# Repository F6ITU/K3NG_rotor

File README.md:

# K3NG_rotor
Yet another K3NG rotator controler pcb

This implementation is based on an Arduino Mega board and a pair of 4x relay boards to drive an AZ-EL antenna system.

Most basic functions are directly driven via Molex KK 254 connectors (up/down, right/left, lcd display output, GPS input, *
I2C extensions... etc). All other "vacant" gpio could be used via solderpads. 

Board could be powered from 8 to 15V 

Source code and wiki should be downloaded at 

https://github.com/k3ng/k3ng_rotator_controller

# Notes de montage

* Les barrettes de contact au pas de 2,54 doivent être soudées après les avoir insérées dans les connecteur gpio de l’Arduino. La série de brasure doit donc être effectuée avec le module MCU en place, lequel servira ainsi de gabarit d’alignement pour les broches. Sans cette précaution, il sera quasiment impossible d’installer l’Arduino sur la carte. 

* Le régulateur de tension doit être le circuit à souder avant tout autre composant. Les deux principaux condensateurs de filtrage sont très proche du 7805 et gêneraient la brasure ce celui-ci s’il était monté a posteriori

* Tous les connecteurs Molex kk254 ne sont pas nécessairement à installer. C’est le cas notamment des entrées gpio « serial » de 0 à 3, qui peuvent être remplacés par de simples jumpers les reliant aux sorties des périphériques installés. Cela permet de choisir sur quel port seront reliés les modules  gps ou Nextion s’il y a lieu

* Toutes les E/S de l’Arduino sont doublées par une rangée de contacts au pas de 2,54, laissant libre toute possibilité d’ajouts de modules exotiques. 

* Les modules « 4 relais » disponibles sur Amazon ou AliExpress sont généralement livrés avec un connecteur « broches  carte à fils » au pas de 2,54mm orientés vers le dessus de la carte. Il est nécessaire de les dessouder et de les remplacer par un connecteur identique, mais soudé « coté piste ». Le shield K3NG doit, pour sa part, être équipé d’un connecteur femelle « carte à carte » pour recevoir la ou les cartes relais en « piggy back ». 

* Deux cartes relais peuvent être installées pour piloter une paire de moteurs azimut/élévation. Prévoir deux entretoises d’une hauteur équivalente aux connecteurs de liaison. 

* ATTENTION : les relais sont commandés « 2 à 2 », soit pour assurer une coupure courants forts, soit pour être utilisés en inverseur (un contact ouvert et un contact fermé au repos, et lycée de Versailles au travail). Cette configuration est notamment nécessaire pour commander les rotor Kantronic/Yaesu/Toyomura d’ancienne génération (split phase ou à phase divisée)

 * Une BOM interactive est disponible sur ce Github dans le répertoire BOM du même métal

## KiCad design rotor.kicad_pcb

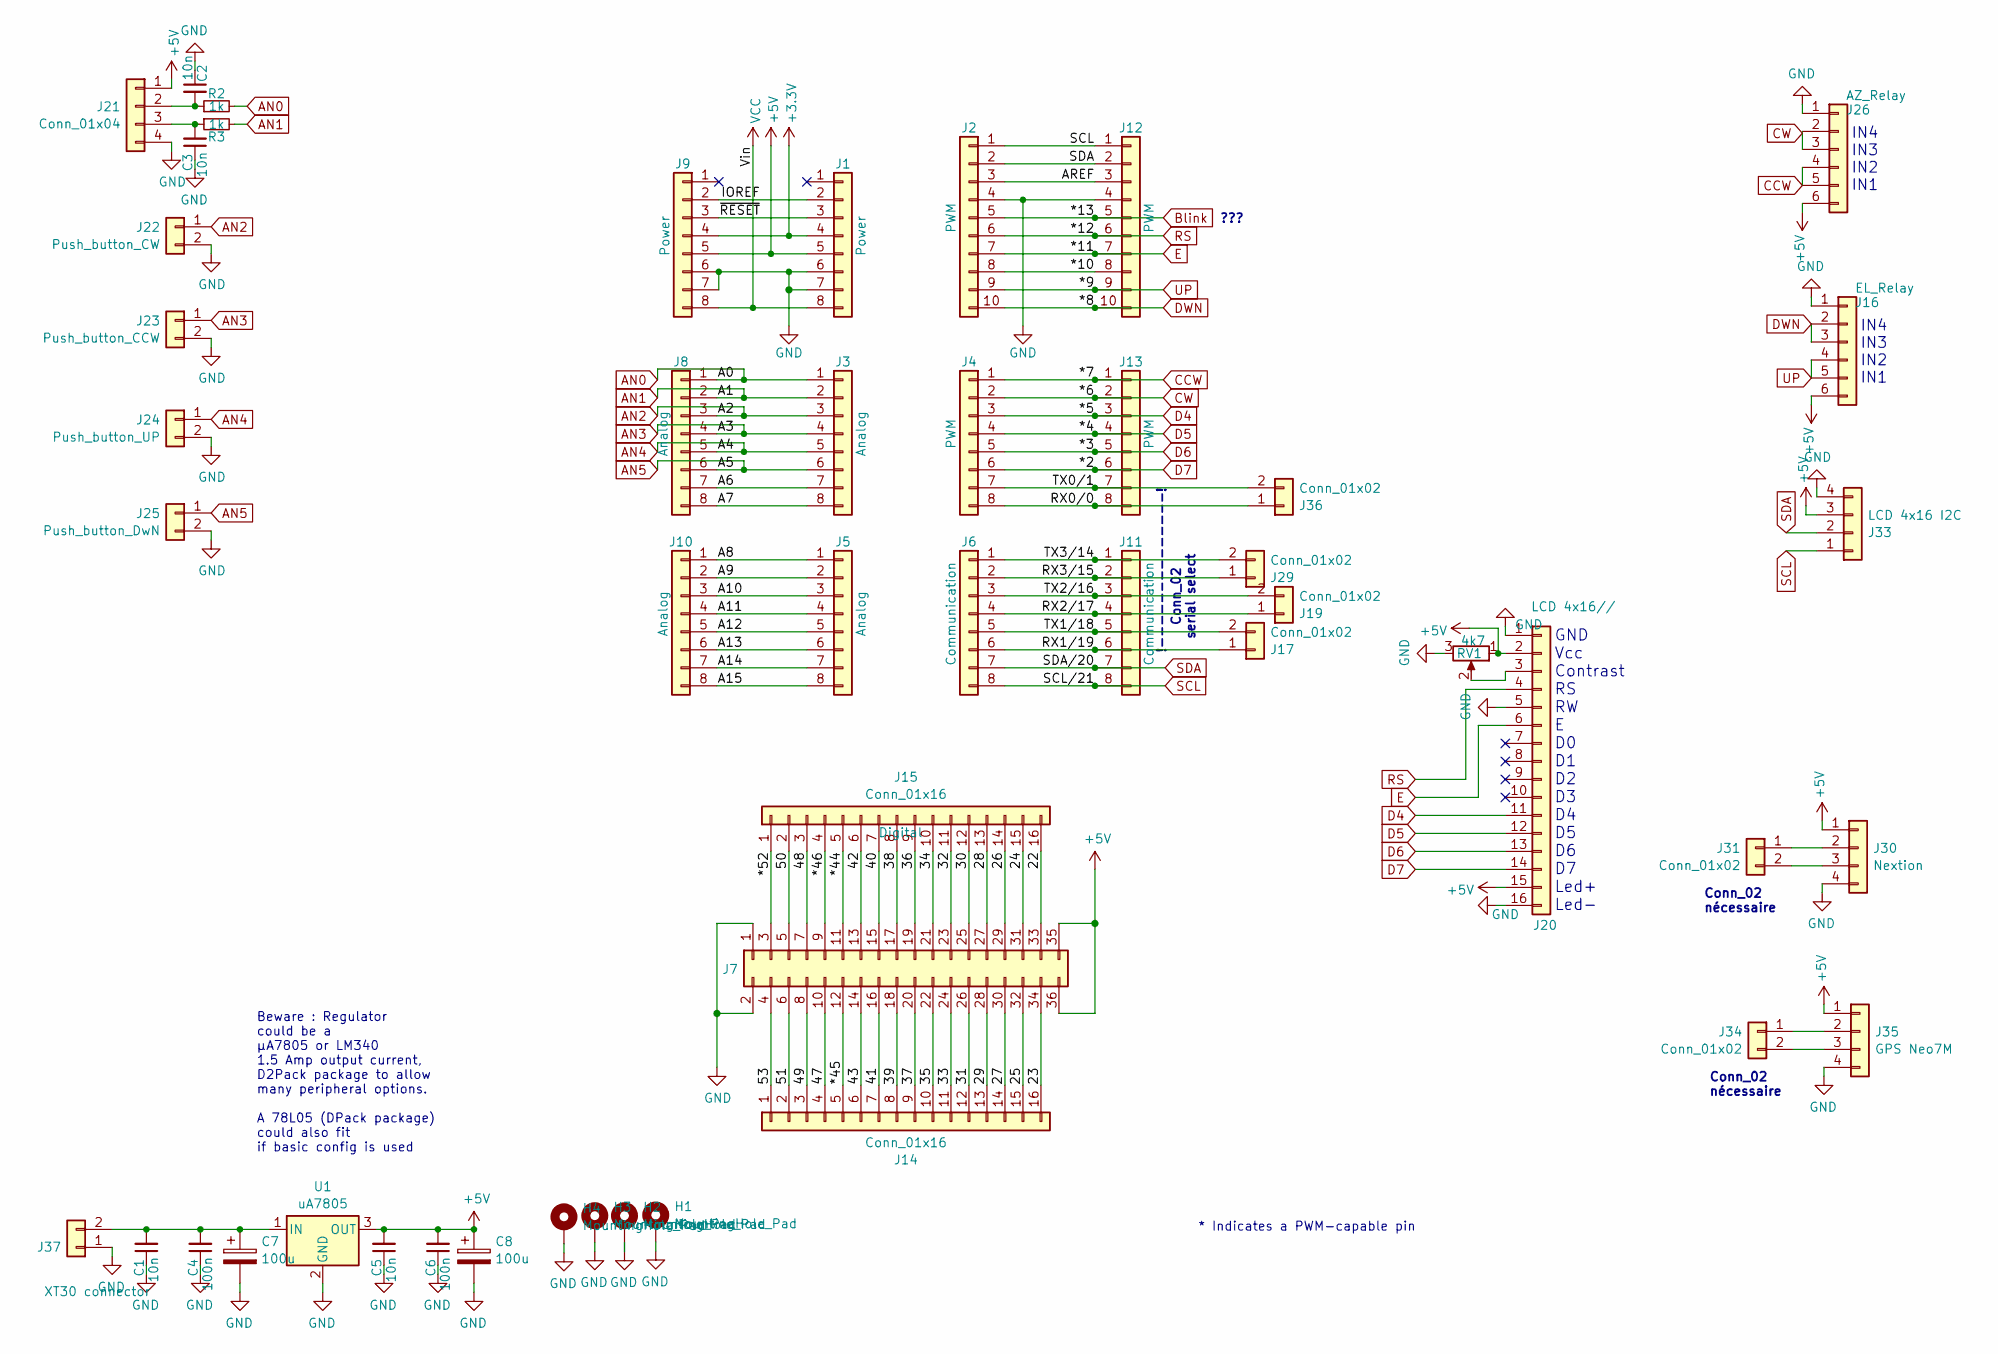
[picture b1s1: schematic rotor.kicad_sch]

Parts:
C1, C2, C3, C5: 10n; C_0805_2012Metric_Pad1.18x1.45mm_HandSolder
C4, C6: 100n; C_0805_2012Metric_Pad1.18x1.45mm_HandSolder
C7, C8: 100u; CP_Elec_10x12.6
H1, H2, H3, H4: MountingHole_Pad; MountingHole_3.5mm_Pad
J1, J9: Power; PinSocket_1x08_P2.54mm_Vertical
J2, J12: PWM; PinSocket_1x10_P2.54mm_Vertical
J3, J8: Analog; PinHeader_1x08_P2.54mm_Vertical
J4, J13: PWM; PinSocket_1x08_P2.54mm_Vertical
J5, J10: Analog; PinSocket_1x08_P2.54mm_Vertical
J6, J11: Communication; PinSocket_1x08_P2.54mm_Vertical
J7: Digital; PinSocket_2x18_P2.54mm_Vertical
J14, J15: Conn_01x16; PinHeader_1x16_P2.54mm_Vertical
J16: EL_Relay; PinSocket_1x06_P2.54mm_Vertical
J17, J19, J29, J31, J34, J36: Conn_01x02; Molex_KK-254_AE-6410-02A_1x02_P2.54mm_Vertical
J20: LCD 4x16//; Molex_KK-254_AE-6410-16A_1x16_P2.54mm_Vertical
J21: Conn_01x04; Molex_KK-254_AE-6410-04A_1x04_P2.54mm_Vertical
J22: Push_button_CW; Molex_KK-254_AE-6410-02A_1x02_P2.54mm_Vertical
J23: Push_button_CCW; Molex_KK-254_AE-6410-02A_1x02_P2.54mm_Vertical
J24: Push_button_UP; Molex_KK-254_AE-6410-02A_1x02_P2.54mm_Vertical
J25: Push_button_DwN; Molex_KK-254_AE-6410-02A_1x02_P2.54mm_Vertical
J26: AZ_Relay; PinSocket_1x06_P2.54mm_Vertical
J30: Nextion; Molex_KK-254_AE-6410-04A_1x04_P2.54mm_Vertical
J33: LCD 4x16 I2C; Molex_KK-254_AE-6410-04A_1x04_P2.54mm_Vertical
J35: GPS Neo7M; Molex_KK-254_AE-6410-04A_1x04_P2.54mm_Vertical
J37: XT30 connector; AMASS_XT30U-F_1x02_P5.0mm_Vertical
R2, R3: 1k; R_0805_2012Metric_Pad1.20x1.40mm_HandSolder
RV1: 4k7; Potentiometer_Bourns_TC33X_Vertical
U1: uA7805; TO-263-3_TabPin2

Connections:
+3V3: J1.4, J9.4
+5V: C5.2, C6.2, C8.1, J1.5, J7.35, J7.36, J9.5, J16.6, J20.2, J20.15, J21.1, J26.6, J30.1, J33.3, J35.1, RV1.1, U1.3 (OUT)
/22: J7.33, J15.16
/23: J7.34, J14.16
/24: J7.31, J15.15
/25: J7.32, J14.15
/26: J7.29, J15.14
/27: J7.30, J14.14
/28: J7.27, J15.13
/29: J7.28, J14.13
/30: J7.25, J15.12
/31: J7.26, J14.12
/32: J7.23, J15.11
/33: J7.24, J14.11
/34: J7.21, J15.10
/35: J7.22, J14.10
/36: J7.19, J15.9
/37: J7.20, J14.9
/38: J7.17, J15.8
/39: J7.18, J14.8
/40: J7.15, J15.7
/41: J7.16, J14.7
/42: J7.13, J15.6
/43: J7.14, J14.6
/47: J7.10, J14.4
/48: J7.7, J15.3
/49: J7.8, J14.3
/50: J7.5, J15.2
/51: J7.6, J14.2
/53: J7.4, J14.1
/*10: J2.8, J12.8
/*44: J7.11, J15.5
/*45: J7.12, J14.5
/*46: J7.9, J15.4
/*52: J7.3, J15.1
/A6: J3.7, J8.7
/A7: J3.8, J8.8
/A8: J5.1, J10.1
/A9: J5.2, J10.2
/A10: J5.3, J10.3
/A11: J5.4, J10.4
/A12: J5.5, J10.5
/A13: J5.6, J10.6
/A14: J5.7, J10.7
/A15: J5.8, J10.8
/AREF: J2.3, J12.3
/IOREF: J1.2, J9.2
/RX0/0: J4.8, J13.8, J36.1
/RX1/19: J6.6, J11.6, J17.1
/RX2/17: J6.4, J11.4, J19.1
/RX3/15: J6.2, J11.2, J29.1
/TX0/1: J4.7, J13.7, J36.2
/TX1/18: J6.5, J11.5, J17.2
/TX2/16: J6.3, J11.3, J19.2
/TX3/14: J6.1, J11.1, J29.2
/~RESET: J1.3, J9.3
AN0: J3.1, J8.1, R2.2
AN1: J3.2, J8.2, R3.2
AN2: J3.3, J8.3, J22.1
AN3: J3.4, J8.4, J23.1
AN4: J3.5, J8.5, J24.1
AN5: J3.6, J8.6, J25.1
Blink: J2.5, J12.5
CCW: J4.1, J13.1, J26.4, J26.5
CW: J4.2, J13.2, J26.2, J26.3
D4: J4.3, J13.3, J20.11
D5: J4.4, J13.4, J20.12
D6: J4.5, J13.5, J20.13
D7: J4.6, J13.6, J20.14
DWN: J2.10, J12.10, J16.2, J16.3
E: J2.7, J12.7, J20.6
GND: C1.1, C2.1, C3.1, C4.1, C5.1, C6.1, C7.2, C8.2, H1.1, H2.1, H3.1, H4.1, J1.6, J1.7, J2.4, J7.1, J7.2, J9.6, J9.7, J12.4, J16.1, J20.1, J20.5, J20.16, J21.4, J22.2, J23.2, J24.2, J25.2, J26.1, J30.4, J33.4, J35.4, J37.1, RV1.3, U1.2 (GND)
unnamed: J20.3, RV1.2
unnamed: C2.2, J21.2, R2.1
unnamed: C3.2, J21.3, R3.1
unnamed: J30.2, J31.1
unnamed: J30.3, J31.2
unnamed: J34.1, J35.2
unnamed: J34.2, J35.3
unnamed: C1.2, C4.2, C7.1, J37.2, U1.1 (IN)
RS: J2.6, J12.6, J20.4
SCL: J2.1, J6.8, J11.8, J12.1, J33.1
SDA: J2.2, J6.7, J11.7, J12.2, J33.2
UP: J2.9, J12.9, J16.4, J16.5
VCC: J1.8, J9.8

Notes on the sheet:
???
IN4 IN3 IN2 IN1
!--------------! Conn_02 serial select
Conn_02 nécessaire
GND Vcc Contrast RS RW E D0 D1 D2 D3 D4 D5 D6 D7 Led+ Led-
* Indicates a PWM-capable pin
Beware : Regulator could be a µA7805 or LM340 1.5 Amp output current, D2Pack package to allow many peripheral options. A 78L05 (DPack package) could also fit if basic config is used

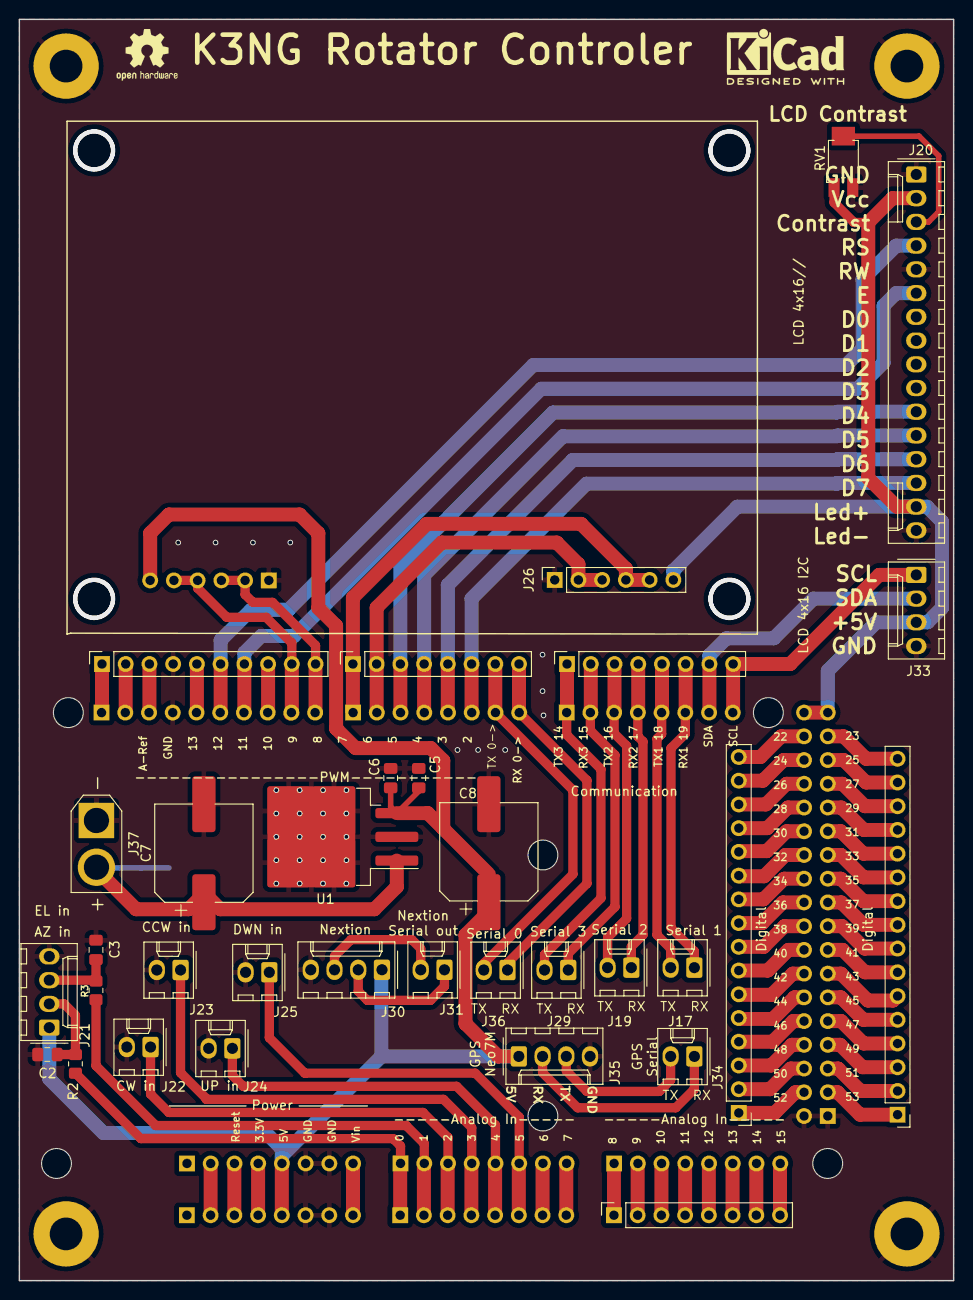
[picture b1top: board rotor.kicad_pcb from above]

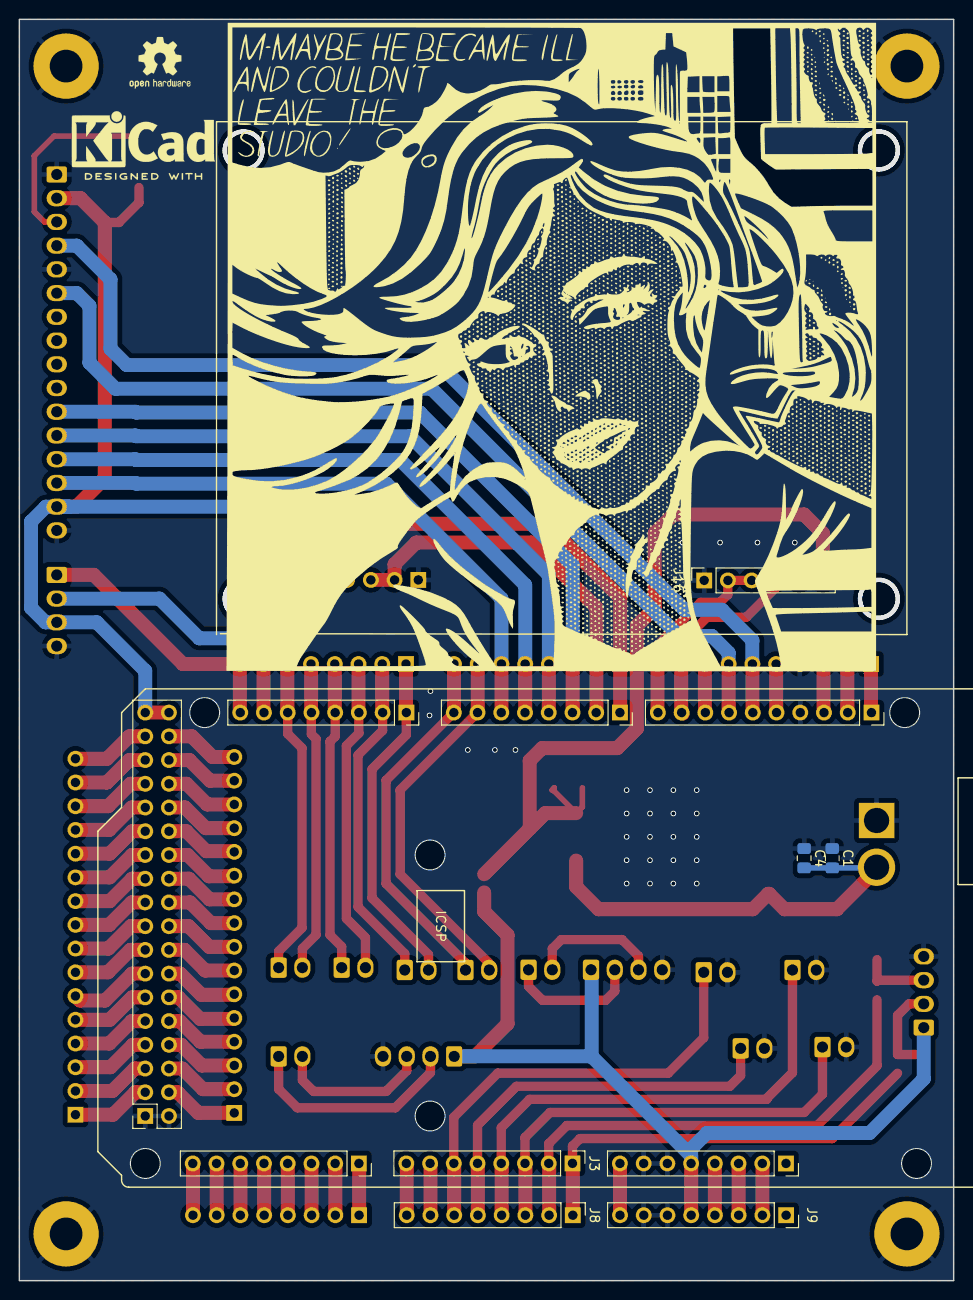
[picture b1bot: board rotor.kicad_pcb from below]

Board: 2 copper layers, 100.0 x 135.0 mm, 55 parts (12 on the bottom side), 85 nets.

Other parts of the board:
MH1, MH2, MH3, MH4, MH5, MH6: MountingHole_3.2mm

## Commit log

2024-01-13 initial release and prototype. Gerber and iBom should be ok
2024-01-13 picture added in the readme
2024-02-12 minor fixes, new iBom, RTM version
2024-02-13 readme updated
2024-11-13 updated schematic pdf
